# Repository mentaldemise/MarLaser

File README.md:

https://github.com/adam-p/markdown-here/wiki/Markdown-Cheatsheet#hr

# Making the K40 not suck, a simple plan.

## WARNINGS:
1. This is not going to go into modifying a RAMPS board to support 24V. 
   * If you're brave enough to try this, then use this [link](https://github.com/ExplodingLemur/presentations/wiki/K40-RAMPS-Conversion) to follow his instructions on modifying the board
2. An ability to either solder or spare cash to purchase parts.

# Baseline

This is a Marlin 2.0 build with all the normal laser options set. This is the same firmware configuration that's used in the top "Result" video. The switch from this to that was Lightburn adding support for Inline mode. A Regular Expression can be run on existing Lightburn output as follows:

* Export your gcode for Marlin to desktop. Open it in Notepad++ then:
  * replace all M03 with “I”
  * replace ^(I.+)[\n](G1.+)$ with $2 $1

^This is very much at your own peril. It works for me. I don't mind breaking my stuff.

# Results for just ramps, no stepper upgrade:

## Materials:

### Note on Materials: The initial write-up here is going to be just for RAMPS, then I'm going to add the stuff for my enclosure for exhaust/cooling/air assist, and then come back and add an addendum for using the LPC1768 board for Raster.

* RAMPS 1.4(Trigorilla or other **24V friendly**) *** MKS Board Sgen L V1
* K40 Breakout or skills 
  * https://oshpark.com/shared_projects/3W1BpcNl 
  * $15USD at https://awesome.tech/product/k40-middlemen-board/
  * BRD and SCH files included below for slim version
  * Connector part is linked from [this](https://github.com/ExplodingLemur/presentations/wiki/K40-RAMPS-Conversion) site, search for "connector for the cable"
* 4 Relay board **
* 5V laser diode **
* 3D Printer
* 24V PSU(Or run relay?) **
* 2A stepper for X(At least)

---
Goal: Make K40 not suck.

Inspiration/Source: http://3dprintzothar.blogspot.com/2014/08/40-watt-chinese-co2-laser-upgrade-with.html

## Breakout wiring
#### Note the Buck converter in this picture is used for something else later on.
These are difficult to see, but on my home-made K40 breakout we have:

|Wire Color| Purpose| Pin|
|-------------|-------------------|---|
|Red| 5V on RAMPS| Any available 5V|
|Black| GND on Ramps| Any available GND|
|4 Pin Dupont| X stepper|X motor|
|White| X Endstop| X- Signal|
|Grey| Y Endstop| Y- Signal|

Use this link to download the Eagle BRD file [Board File](media/k40_breakout/K40_MiddleMan_002A.brd)  
Use this link to download the Eagle SCH file [Board Schematic](media/k40_beakout/K40_MiddleMan_002A.sch)

## Board mount
I used [This thing](https://www.thingiverse.com/thing:2155376) to mount the Trigorilla board in my case. You can find others that will work for whatever RAMPS variant you have. The inpiration link above I think has one for a regule RAMPS even.

## Wiring RAMPS to Laser PSU
PSU Wiring:
#### Note that you may need to check the pinout on your PSU

Top connector(top to bottom)
* NC
* 5V going to any open 5V pin on RAMPS
* GND going to - of 5A input on RAMPS
* +24V going to + of 5A input on RAMPS
---
Bottom Connector(top to bottom)
* NC
* Laser PWM - 6 -- There are only certain pins this can go on because of timers. Leave it on 6 to be safe.
* GND going to any open - on RAMPS
* Laser Enable/Fire - 5 - This is just a digital IO so you can use whichever you want - 10K resistor to +5V here to stop sporadic turnon during boot if interlock is off
* One side of enable push-button toggle
* Other side of enable push-button toggle
---

## Step Calibration
An important part of getting Marlin right on your machine is making sure that distances are correct. If you move 20MM in X when you thought you were going 19MM then there's a bit problem.

This LightBurn file can be used to calibrate steps. There's a 20mmX20mm square with 5mm intervals and axis labels. Cut the outside and etch the inside, measure, and adjust until you get 20x20 with a caliper. Then cut the two triangles(one is rotated 90 degrees), if the two triangles stack up the same then your steps are at least correctly proportioned. 

Use this link to download the Calibration file [Calibration File](media/calibration/20mmSquareStepCal.lbrn)  

~~### 12V buck for Relays
Stepping 24V down to 5V to run switches and the relay coils~~

### Relay board
Runs: Cooling(water pump), Exhaust, and Air Assist via panel buttons

### Panel

Here's the new panel I have hooked up. The relay board will better explain, but the push buttons are feeding power to a relay in all cases but the aiming diode.

Here is the [DXF File](media/panel_files/NewPanel.dxf)
Here is the [LBRN File](media/panel_files/LaserPanel.lbrn)

## Water pump/flow indicator?

*** When hooking up the chiller and cutting my speed/power for MDF went from 10/32 to barely get through to 10/28.

This setup works just fine without the chiller in the loop for the K40 if you turn your pump off between using the laser. I found after a few hours the pump alone would heat the water up(only having 5Gallons doesn't help)

We have an aquarium pump in the bottom of a 5 gallon bucket.  
Outlet on it goes to the IN side of a chiller.  
Outlet of the chiller goes to the IN side of a 12V generator.   
Outlet of the generator then goes to the laser in.

Generator output then goes to the "FLOW" led on the panel. This needs some revision yet.  
There's a Thermistor stuck to the side of the bucket the pump is in and hooked up to TH0 on the RAMPS board to get water temp on the screen as well.

Water pump is controlled via one of the panel buttons and a relay using one of the original outlets on the back of the case(with wiring corrected)

**wire cleanup will come when I get my panel mount connectors this coming week.

## MKS Upgrade for Raster
---

---

Case was printed using [This thing](https://www.thingiverse.com/thing:4174973) and [this cooling duct](https://www.thingiverse.com/thing:4191051).

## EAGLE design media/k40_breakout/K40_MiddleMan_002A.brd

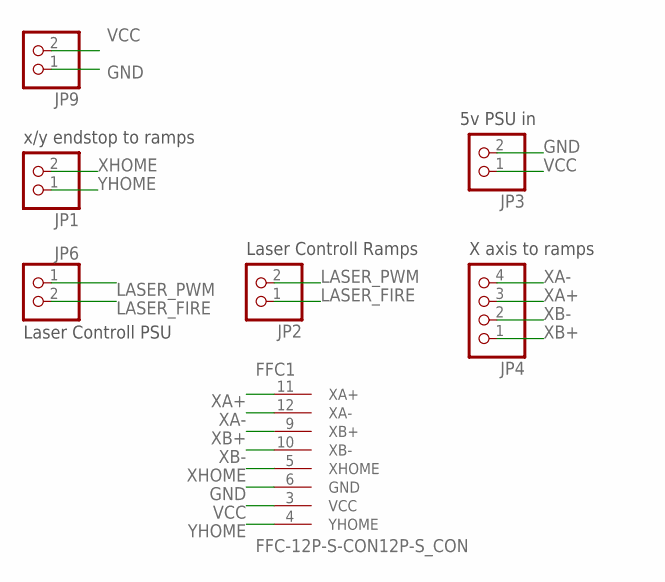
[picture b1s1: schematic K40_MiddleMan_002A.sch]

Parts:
FFC1: FFC-12P-S-CON12P-S_CON; FFC
JP1, JP2, JP3, JP6, JP9: PINHD-1X2; 1X02
JP4: PINHD-1X4; 1X04

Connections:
GND: FFC1.6 (GND), JP3.2, JP9.1
LASER_FIRE: JP2.1, JP6.2
LASER_PWM: JP2.2, JP6.1
VCC: FFC1.3 (VCC), JP3.1, JP9.2
XA+: FFC1.11 (XA+), JP4.3
XA-: FFC1.12 (XA-), JP4.4
XB+: FFC1.9 (XB+), JP4.1
XB-: FFC1.10 (XB-), JP4.2
XHOME: FFC1.5 (XHOME), JP1.2
YHOME: FFC1.4 (YHOME), JP1.1

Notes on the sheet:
5v PSU in
X axis to ramps
Laser Controll Ramps
Laser Controll PSU
x/y endstop to ramps

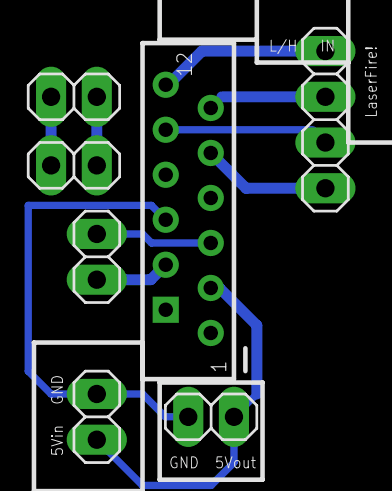
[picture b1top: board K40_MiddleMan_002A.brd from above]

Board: 2 copper layers, 7 parts (0 on the bottom side), 10 nets.

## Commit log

2020-05-13 Moving from BitBucket.
2020-05-13 Testing adding YouTube vid to readme
2020-05-13 Embed instead?
2020-05-14 Adjusting steps on X asix for swapped in new stepper, also adjusting Y after calibration test. LB file included, use the square until you get 20 on each then verify with the two triangles.
2020-05-14 Adding step calibration to readme.
2020-05-15 Fixing steps and setting current to more reasonable values. :D EEPROM is still an issue, may need to merge in latest changes.
2020-05-15 Latest MKS setting tweaks. No idea what I'm doing. Trying to slam the head back and forth faster with the 2A stepper.
2020-05-15 Fleshing out cooler setup now that chiller arrived.
2020-05-15 Fixing LPC videos.
2020-05-16 About to pull changes and turn off TMC stuff to save CPU cycles.
2020-05-16 Turning off TMC stuff to save CPU cycles.
2020-05-16 Pulling in latest changes from upstream.
2020-05-22 Adding messed up panel with upside down ammeter like original
2020-05-22 Setting changes for swapped in Y motor(1.8A with dual shaft)
2020-05-22 better version but "Enable" was noticed to be seen missing(hidden under bezel)
2020-05-22 Adding K40 panel to readme
